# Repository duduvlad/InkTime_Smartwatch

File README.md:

# InkTime Smartwatch

Un smartwatch open-source cu ecran E-Paper, construit în jurul SoC-ului Nordic nRF52840. Proiectul acoperă etapa de Engineering Validation (EVT): design-ul hardware complet (schematic + PCB), fișierele de fabricație și modelul 3D al ansamblului.

## Cuprins

- [Diagrama Bloc](#diagrama-bloc)
- [Descriere Hardware](#descriere-hardware)
- [Pinout nRF52840](#pinout-nrf52840)
- [Bill of Materials](#bill-of-materials)
- [Estimare Consum Energetic](#estimare-consum-energetic)
- [Decizii de Design și Constrângeri](#decizii-de-design-și-constrângeri)
- [Imagini](#imagini)
- [Structura Repository-ului](#structura-repository-ului)
- [Licență](#licență)

---

## Diagrama Bloc
 
```
                          ┌─────────────────────────────────┐
                          │         nRF52840 (U1)           │
                          │       SoC + BLE Radio           │
                          │                                 │
          ┌───────────────┤ P0.06 (SDA)     P0.02 (SCK)    ├──── SPI ────┐
          │  I2C Bus      │ P0.07 (SCL)     P0.03 (MOSI)   │             │
          │               │                 P0.05 (CS)      │             │
          │               │                 P0.15 (DC)      │             │
          │               │                 P0.16 (RST)     │             │
          │               │                 P0.17 (BUSY)    │             │
          │               │                                 │             │
          │               │ P0.13 ──── SW_UP (buton)        │    ┌────────┴────────┐
          │               │ P0.14 ──── SW_ENTER (buton)     │    │  E-Paper 1.54"  │
          │               │ P1.02 ──── SW_DOWN (buton)      │    │  (via FPC J1)   │
          │               │                                 │    └─────────────────┘
          │               │ P0.12 ──── HAPTIC_EN (DRV2605)  │
          │               │ P0.08 ──── IMU_INT1             │
          │               │ P1.08 ──── IMU_INT2             │
          │               │ P0.10 ──── ALERT (fuel gauge)   │
          │               │ P0.11 ──── PMIC_INT (charger)   │
          │               │ P1.01 ──── EPD_PWR (MOSFET)     │
          │               │                                 │
          │               │ D+/D- ──── USB-C (J4)           │
          │               │ SWDIO/SWDCLK ── Debug (J2)      │
          │               │                                 │
          │               │ ANT (H23) ── Antenă 2.4GHz      │
          │               └─────────────────────────────────┘
          │
     ┌────┴─────────────────────────────────────────────────┐
     │                   Magistrala I2C                      │
     │   (SDA = P0.06, SCL = P0.07, pull-up 3.3kΩ)         │
     ├──────────────┬──────────────┬─────────────┬──────────┤
     │              │              │             │          │
┌────┴────┐  ┌─────┴─────┐  ┌────┴────┐  ┌────┴────┐     │
│ BMA423  │  │ DRV2605   │  │MAX17048 │  │BQ25180  │     │
│  (IC3)  │  │  (IC2)    │  │  (U3)   │  │ (IC1)   │     │
│  IMU    │  │ Haptic    │  │  Fuel   │  │ Charger │     │
│         │  │ Driver    │  │  Gauge  │  │         │     │
└─────────┘  └───────────┘  └────┬────┘  └────┬────┘     │
                                 │             │          │
                            ┌────┴─────────────┴────┐     │
                   ┌───────>│  Baterie LiPo 250mAh  │     │
                   │        │    AKYGA LP502030      │     │
                   │        └───────────┬────────────┘     │
                   │                    │ VREG (SYS)       │
              USB-C (J4)         ┌──────┴──────┐           │
              VBUS ─────────────>│  RT6160     │           │
                                 │  (IC9)      │           │
                                 │  Buck-Boost │           │
                                 └──────┬──────┘           │
                                        │                  │
                                    3.3V Rail ─────────────┘
```

---

## Descriere Hardware

Inima proiectului este **nRF52840** — un SoC cu procesor ARM Cortex-M4F la 64 MHz, 1 MB Flash și 256 KB RAM, plus radio BLE 5.0 integrat. Pe lângă logica principală, el controlează direct toate perifericele de pe placă.

**Managementul energiei** funcționează într-un lanț: USB-C → BQ25180 (charger LiPo) → baterie AKYGA LP502030 (250 mAh, 3.7V) → RT6160 (buck-boost) → 3.3V stabil pentru tot sistemul. Tensiunea bateriei este monitorizată de un fuel gauge MAX17048, care trimite alerte prin I2C și pin-ul ALERT când bateria scade sub praguri configurabile. Charger-ul BQ25180 comunică și el pe I2C, permițând configurarea curentului de încărcare, iar pin-ul !INT semnalează evenimente (încărcare completă, erori termice, etc.).

**Afișajul** este un ecran E-Paper de 1.54" conectat printr-un flex cable (FPC de 24 pini, conector Molex 503480-2400). E-Paper-ul consumă curent doar la refresh și își menține imaginea fără alimentare. Alimentarea display-ului este controlată separat prin P1.01, care comandă un MOSFET P-channel (DMG2305UX-7) — astfel display-ul poate fi oprit complet pentru a economisi energie. Comunicația cu display-ul se face pe SPI, cu pini adiționali de control (DC, RST, BUSY).

**Senzorul de mișcare** BMA421/BMA423 (accelerometru triaxial, 12 biți) este pe magistrala I2C și oferă două ieșiri de întrerupere (INT1 pe P0.08 și INT2 pe P1.08). Este folosit pentru numărarea pașilor, detecția gesturilor (raise-to-wake) și orientarea ecranului. Pin-ul SDO al senzorului este legat la GND prin R3, ceea ce setează adresa I2C la 0x18.

**Feedback haptic**: un motor de vibrații controlat de DRV2605 (driver dedicat cu bibliotecă internă de efecte). Driverul primește comenzi pe I2C și este activat/dezactivat de P0.12 (EN). Ieșirile OUT+ și OUT- merg la motorul haptic (shaker), cu test pad-uri pe placă pentru debugging.

**Butoanele**: trei butoane push (UP, ENTER, DOWN) cu rezistențe de pull-up de 10kΩ la 3.3V și condensatoare de debouncing de 1µF pe fiecare. Sunt active pe LOW — apăsarea trage pinul la GND.

**Conectivitate BLE**: antena ceramică Johanson 2450AT18B100E, conectată la pinul ANT al nRF52840 printr-o rețea de impedanță matching (L1 = 3.9nH, C3 = 1pF, C4 = 1pF). Zona de sub antenă este decupată din toate cele trei planuri de masă.

**Debug/Programare**: interfață SWD (SWDIO, SWDCLK) rutată la conectorul Tag-Connect TC2030-IDC (J2) și la test pad-uri. Pin-ul SWO (P1.00) este disponibil și el pe test pad pentru trace output.

---

## Pinout nRF52840

Tabelul de mai jos detaliază fiecare pin utilizat al microcontroller-ului, cu referința la ball-ul din pachetul aQFN (7x7 mm, 73 pini).

| Pin nRF52840 | Ball | Net / Semnal | Destinație | Notă |
|:---|:---|:---|:---|:---|
| P0.00/XL1 | D2 | P0.00/XL1 | Crystal 32.768 kHz (X2) | Low-frequency clock |
| P0.01/XL2 | F2 | P0.01/XL2 | Crystal 32.768 kHz (X2) | Low-frequency clock |
| P0.02/AIN0 | A12 | SCK | E-Paper SPI Clock | SPI master |
| P0.03/AIN1 | B13 | MOSI | E-Paper SPI Data | SPI master |
| P0.05/AIN3 | K2 | EPD_CS | E-Paper Chip Select | SPI CS, active LOW |
| P0.06 | L1 | SDA | Magistrala I2C - Data | BQ25180, BMA423, DRV2605, MAX17048 |
| P0.07 | M2 | SCL | Magistrala I2C - Clock | Pull-up 3.3kΩ la 3V3 |
| P0.08 | N1 | IMU_INT1 | BMA423 Interrupt 1 | Step counter, gesture detection |
| P0.10/NFC2 | J24 | ALERT | MAX17048 Battery Alert | Active LOW |
| P0.11 | T2 | PMIC_INT | BQ25180 !INT | Semnalizare stare încărcare |
| P0.12 | U1 | HAPTIC_EN | DRV2605 Enable | Activare driver haptic |
| P0.13 | AD8 | SW_UP | Buton UP | Pull-up 10kΩ (R5), debounce 1µF (C30) |
| P0.14 | AC9 | SW_ENTER | Buton ENTER | Pull-up 10kΩ (R8), debounce 1µF (C31) |
| P0.15 | AD10 | EPD_DC | E-Paper Data/Command | HIGH = date, LOW = comandă |
| P0.16 | AC11 | EPD_RST | E-Paper Reset | Active LOW |
| P0.17 | AD12 | EPD_BUSY | E-Paper Busy | HIGH = display ocupat |
| P0.18/RESET | AC13 | RESET | System Reset | Rutat la TP_RESET și J2 |
| P1.00 | AD22 | SWO | Serial Wire Output | Debug trace, rutat la TP_SWO |
| P1.01 | Y23 | EPD_PWR | MOSFET gate (DMG2305UX) | Controlează alimentarea display-ului |
| P1.02 | W24 | SW_DOWN | Buton DOWN | Pull-up 10kΩ (R7), debounce 1µF (C29) |
| P1.08 | P2 | IMU_INT2 | BMA423 Interrupt 2 | Al doilea canal de întrerupere |
| D+ | AD6 | D+ | USB-C Data+ | Prin ESD protection (USBLC6-2SC6Y) |
| D- | AD4 | D- | USB-C Data- | Prin ESD protection (USBLC6-2SC6Y) |
| VBUS | AD2 | VBUS | USB VBUS sense | Detectare conexiune USB |
| SWDIO | AC24 | SWDIO | SWD Debug Data | Rutat la J2 (TC2030) și TP |
| SWDCLK | AA24 | SWDCLK | SWD Debug Clock | Rutat la J2 (TC2030) și TP |
| XC1 | B24 | - | Crystal 32 MHz (X1) | High-frequency clock |
| XC2 | A23 | - | Crystal 32 MHz (X1) | High-frequency clock |
| ANT | H23 | ANT | Rețea matching + Antenă | 2.4 GHz BLE |
| VDDH | Y2 | 3V3 | Alimentare high voltage | 3.3V |
| VDD (multiple) | W1, AD14, B1, A22, AD23 | 3V3 | Alimentare digitală | Fiecare cu condensator de decuplare |
| DCC | B3 | - | DC/DC inductor intern | L2 (10µH) |
| DEC1-6 | diverse | - | Decoupling intern nRF | Condensatoare conform datasheet-ului |

**Pini liberi** (neconectați, disponibili pentru extensii viitoare): P0.04, P0.09, P0.19–P0.31, P1.03–P1.07, P1.09–P1.15.

---

## Bill of Materials

### Componente principale

| Componentă | MFR Part Number | Descriere | JLCPCB Part # | Datasheet |
|:---|:---|:---|:---|:---|
| nRF52840 (U1) | NRF52840-QFAA | SoC BLE 5.0, ARM Cortex-M4F, aQFN-73 | [C190794](https://jlcpcb.com/partdetail/NordicSemicon-NRF52840_QIAAR/C190794) | [Nordic](https://infocenter.nordicsemi.com/pdf/nRF52840_PS_v1.8.pdf) |
| BQ25180 (IC1) | BQ25180YBGR | Charger LiPo, I2C configurabil, BGA-8 | [C3682423](https://jlcpcb.com/partdetail/TexasInstruments-BQ25180YBGR/C3682423) | [TI](https://www.ti.com/lit/ds/symlink/bq25180.pdf) |
| DRV2605 (IC2) | DRV2605YZFR | Haptic driver ERM/LRA, I2C, BGA-9 | [C81079](https://jlcpcb.com/partdetail/TexasInstruments-DRV2605YZFR/C81079) | [TI](https://www.ti.com/lit/ds/symlink/drv2605.pdf) |
| BMA423 (IC3) | BMA423 | Accelerometru triaxial, 12-bit, I2C, LGA-12 | [C437656](https://jlcpcb.com/parts) | [Bosch](https://www.bosch-sensortec.com/media/boschsensortec/downloads/datasheets/bst-bma423-ds000.pdf) |
| RT6160 (IC9) | RT6160AWSC | Buck-Boost DC/DC, I2C, WL-CSP-15 | [C20621404](https://jlcpcb.com/parts) | [Richtek](https://www.richtek.com/assets/product_file/RT6160A/DS6160A-05.pdf) |
| MAX17048 (U3) | MAX17048G+T10 | Fuel gauge LiPo, I2C, TDFN-8 | [C2682616](https://jlcpcb.com/partdetail/MaximIntegrated-MAX17048GT10/C2682616) | [Analog Devices](https://datasheets.maximintegrated.com/en/ds/MAX17048-MAX17049.pdf) |
| Antenă BLE (ANT1) | 2450AT18B100E | Antenă ceramică 2.4 GHz, 1206 | - | [Johanson](https://www.johansontechnology.com/datasheets/2450AT18B100/2450AT18B100.pdf) |
| FPC Connector (J1) | 503480-2400 | Molex 24-pin FPC, 0.5mm pitch | - | [Molex](https://www.molex.com/en-us/products/part-detail/5034802400) |
| USB-C (J4) | KH-TYPE-C-16P | Connector USB-C 16 pini, Kinghelm | - | [Kinghelm](https://www.snapeda.com/parts/KH-TYPE-C-16P/Kinghelm/view-part/) |
| Tag-Connect (J2) | TC2030-IDC | Conector debug SWD, 6 pini | - | [Tag-Connect](https://www.tag-connect.com/product/tc2030-idc) |
| ESD Protection (D3) | USBLC6-2SC6Y | TVS diode array, USB ESD, SOT-23-6 | - | [ST](https://www.st.com/resource/en/datasheet/usblc6-2.pdf) |
| MOSFET P-ch | DMG2305UX-7 | P-MOSFET, 20V/4.2A, SOT-23 | - | [Diodes Inc.](https://www.diodes.com/assets/Datasheets/DMG2305UX.pdf) |
| MOSFET N-ch (Q3) | SI1308EDL-T1-GE3 | N-MOSFET, 30V/1.5A, SC-70 | - | [Vishay](https://www.vishay.com/docs/63399/si1308edl.pdf) |
| Schottky Diodes (D2,D4,D5) | MBR0530 | 30V/0.5A, SOD-123 | - | [ON Semi](https://www.onsemi.com/pdf/datasheet/mbr0520-d.pdf) |
| Butoane (x3) | EVP-AKE31A | Push button, Panasonic | - | [Panasonic](https://industrial.panasonic.com/cdbs/www-data/pdf/ATV0000/ATV0000CE3.pdf) |
| Crystal 32 MHz (X1) | - | XTAL 2016 package | - | - |
| Crystal 32.768 kHz (X2) | - | XTAL 3215 package | - | - |
| Inductor (L7) | FTC252012SR47MBCA | 0.47µH, 2520, TDK | [C5832368](https://jlcpcb.com/partdetail/6763488-FTC252012SR47MBCA/C5832368) | [TDK](https://product.tdk.com/en/search/inductor/inductor/smd/info?part_no=FTC252012SR47MBCA) |

### Pasive (sumarizat)

| Tip | Valori | Capsulă | Cantitate |
|:---|:---|:---|:---|
| Rezistențe 0201 | 0.47Ω, 2.2Ω, 3.3kΩ, 5.1kΩ, 7.68kΩ, 10kΩ | 0201 (0.6x0.3mm) | ~20 buc |
| Condensatoare ≤100nF | 1pF, 12pF, 47nF, 100pF, 100nF | 0201 | ~15 buc |
| Condensatoare >100nF | 1µF, 4.7µF, 10µF, 22µF | 0402 | ~25 buc |
| Inductori | 3.9nH, 10µH, 15µH, 68µH | 0402 | 4 buc |

Lista completă se regăsește în [`Manufacturing/BOM.csv`](Manufacturing/BOM.csv), iar coordonatele de asamblare în [`Manufacturing/PickAndPlace.csv`](Manufacturing/PickAndPlace.csv).

---

## Estimare Consum Energetic

Valorile sunt extrase din datasheet-urile componentelor, pentru modul activ și sleep.

| Componentă | Mod Activ | Mod Sleep / Idle | Notă |
|:---|:---|:---|:---|
| nRF52840 (CPU @ 64MHz) | ~5 mA | ~1.5 µA (System OFF) | CPU + Radio off în sleep |
| nRF52840 (BLE TX) | ~5–8 mA (0 dBm) | - | Transmisie BLE la 0 dBm |
| E-Paper 1.54" | ~15–25 mA (refresh) | ~0 µA | Consum doar la refresh, ~2-3s/refresh |
| BMA423 | ~150 µA | ~14 µA (low-power) | Accelerometru în modul low-power |
| MAX17048 | ~23 µA | ~3 µA (hibernate) | Fuel gauge, citiri periodice |
| BQ25180 | ~1 mA (charging) | ~1 µA (standby) | Consum propriu, fără curentul de încărcare |
| DRV2605 | ~10 mA (activ, cu motor) | ~650 µA (standby) | Standby cu EN LOW |
| RT6160 | ~30 µA (quiescent) | ~30 µA | Eficiența >90% la sarcini mici |

**Estimare viață baterie (250 mAh)**:
- *Standby pur* (ecran static, BLE off, CPU sleep): ~1.5µA + 14µA + 3µA + 1µA + 30µA ≈ **50 µA** → ~5000 ore (~208 zile)
- *Utilizare normală* (10 refresh-uri display/oră, BLE advertising, step counting): consum mediu estimat la **~0.3–0.5 mA** → ~500–830 ore (~21–35 zile)
- *Utilizare intensă* (BLE conectat, refresh-uri frecvente, haptic): consum mediu ~2–5 mA → ~2–5 zile

Aceste estimări sunt teoretice; consumul real va depinde de firmware și pattern-urile de utilizare.

---

## Decizii de Design și Constrângeri

### Reguli PCB respectate
- **Dimensiune PCB**: ~46 x 35 mm (forme octogonale cu decupaje pentru butoane), grosime 1 mm
- **Stackup 4 layere**:
  - **TOP**: componente + rutare + ground pour
  - **Inner 1**: rutare + ground pour
  - **Inner 2**: rutare + ground pour
  - **BOTTOM**: nefolosit (layer-ul a fost lăsat gol conform cerințelor)
- **Componente**: toate amplasate exclusiv pe TOP
- **Trasee de putere** (VBUS, VREG, 3V3, VBAT): width = 0.3 mm, subțiate doar sub BGA-uri unde spațiul impune
- **Trasee de date**: minimum 0.15 mm
- **Fără unghiuri de 90°** pe niciun traseu
- **Condensatoare de decuplare** (100nF): plasate imediat lângă pinii VDD ai fiecărui IC — în cazul nRF52840, câte un condensator per grup de pini VDD (C6, C7, C8, C12, C14 pe 3V3)
- **Via stitching** între cele trei planuri de masă (TOP, Inner 1, Inner 2), cu densitate crescută în zona circuitului radio pentru impedanță scăzută a căii de retur

### Antena
- Antena ceramică (ANT1) este plasată pe marginea de sus a PCB-ului (cea mai depărtată de corpul utilizatorului)
- **Decupaj complet** al cuprului sub antenă pe toate cele trei layere cu ground pour (TOP, Inner 1, Inner 2) — nicio rutare în acea zonă
- Rețea de matching: L1 (3.9nH), C3 (1pF), C4 (1pF) conform recomandărilor Nordic

### Alimentarea display-ului
- Display-ul E-Paper are nevoie de tensiuni de drive mari (±15V–20V) generate intern de circuitul display-ului
- Alimentarea display-ului este comutată printr-un MOSFET P-channel (DMG2305UX-7) controlat de P1.01 prin N-MOSFET Q3 (SI1308EDL)
- Circuitul include diode Schottky (MBR0530) pentru protecția tensiunilor inverse de la pompele de sarcină ale display-ului
- Inductorul L5 (68µH) și condensatoarele asociate filtrează alimentarea display-ului

### Bateria
- AKYGA LP502030: 250 mAh, 3.7V nominal, dimensiuni 32.5 × 21 × 5.5 mm
- Conectată direct la test pad-uri (TP_VBAT, TP_BAT_GND) prin lipire — nu se folosește conectorul JST pentru a economisi spațiu
- Modelul 3D al bateriei este inclus în ansamblul mecanic

### Test Pad-uri
Placa dispune de 14 test pad-uri marcate clar în silkscreen, permițând debugging fără nevoie de conectori:

| Test Pad | Semnal | Scop |
|:---|:---|:---|
| TP_3.3V / TP_3V3 | 3V3 | Verificare alimentare principală |
| TP_VREG | VREG/SYS | Ieșire charger → intrare DC/DC |
| TP_VBAT | VBAT | Tensiune baterie |
| TP_BAT_GND | GND | GND baterie (punct de lipire) |
| TP_GND | GND | Masă de referință |
| TP_SDA | SDA | I2C Data (debugging) |
| TP_SCL | SCL | I2C Clock (debugging) |
| TP_SWDIO | SWDIO | Debug SWD |
| TP_SWDCLK | SWDCLK | Debug SWD |
| TP_SWO | SWO | Serial Wire Output |
| TP_RESET | RESET | Reset manual |
| TP_OP | OUT+ | Ieșire haptic + |
| TP_ON | OUT- | Ieșire haptic - |

### DRC și ERC
- Design-ul trece verificarea DRC cu fișierul de reguli furnizat
- Erori acceptate și documentate:
  - **"Only INPUT pins on NET"** — eroare cosmetică, ignorată conform specificațiilor proiectului
  - **Overlap la test pad-uri** — TP-urile sunt dimensionate generos intenționat pentru ușurința accesului cu sonde
  - **Erori Dimension la butoane și USB-C** — cauzate de decupajele din conturul plăcii, neglijate conform cerințelor

### Silkscreen
- Layer-ul de silkscreen conține doar **designator-urile componentelor** (C1, R5, IC1 etc.), fără valori
- Test pad-urile sunt etichetate cu numele semnalelor pe care le poartă
- Orientarea textelor este uniformă pentru lizibilitate

---

## Imagini

### Schema electrică

**Pagina 1 — MCU, Power, IMU, SWD:**

**Pagina 2 — E-Paper, Haptic, Butoane, USB-C:**

### Layout PCB (TOP)

### PCB3D

### CARCASA

---

## Structura Repository-ului

```
InkTime_Smartwatch/
├── Hardware/
│   ├── Schematic.sch          # Schema electrică (Eagle/Fusion 360)
│   └── PCB.brd                # Layout-ul PCB (Eagle/Fusion 360)
├── Manufacturing/
│   ├── gerbers.zip            # Fișiere Gerber pentru fabricație PCB
│   ├── BOM.bom                # Bill of Materials complet
│   └── PickAndPlace.cpl       # Coordonate de asamblare SMT
├── Mechanical/
│   ├── WearAwareNewCase.step  # Model 3D complet (PCB + baterie + display + carcasă)
│   └── WearAwareNewCase.3mf   # Model 3D format 3MF
│   └── PCB.step                   # Model 3D al PCB-ului cu componente
├── Images/
│   ├── Schematic1.jpeg       # Schema electrică - MCU, Power, IMU, SWD
│   ├── Schematic2.jpeg # Schema electrică - E-Paper, Haptic, USB-C
│   └── Pcb.jpeg            # Layout PCB - vedere TOP
│   ├── PCB3D.jpeg                 # Randare 3D a PCB-ului
│   └── Carcasa.jpeg               # Randare carcasă
├── LICENSE                    # Apache License 2.0
└── README.md                  # Acest fișier
```

---

## Licență

Proiect open-source, licențiat sub [Apache License 2.0](LICENSE).

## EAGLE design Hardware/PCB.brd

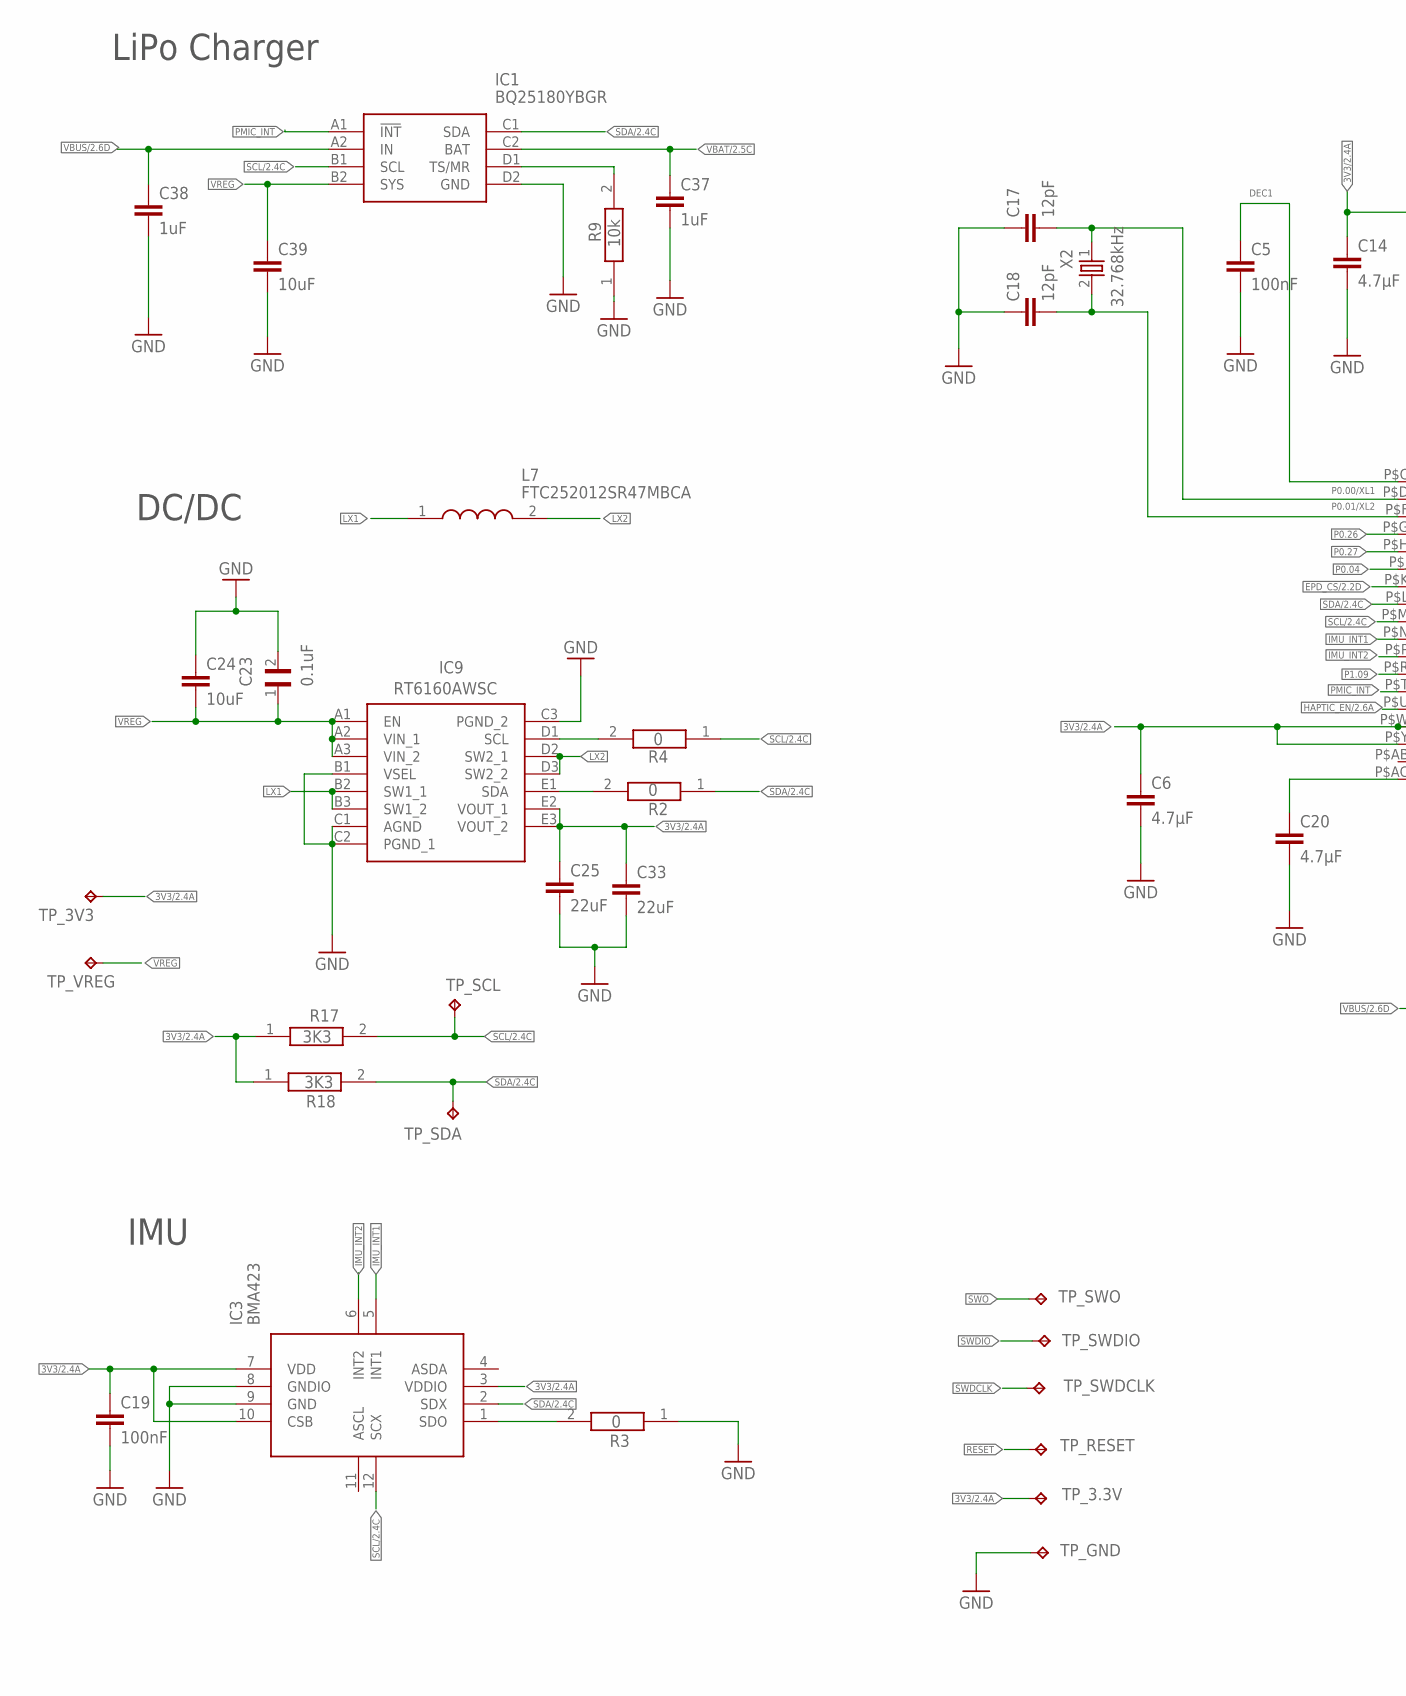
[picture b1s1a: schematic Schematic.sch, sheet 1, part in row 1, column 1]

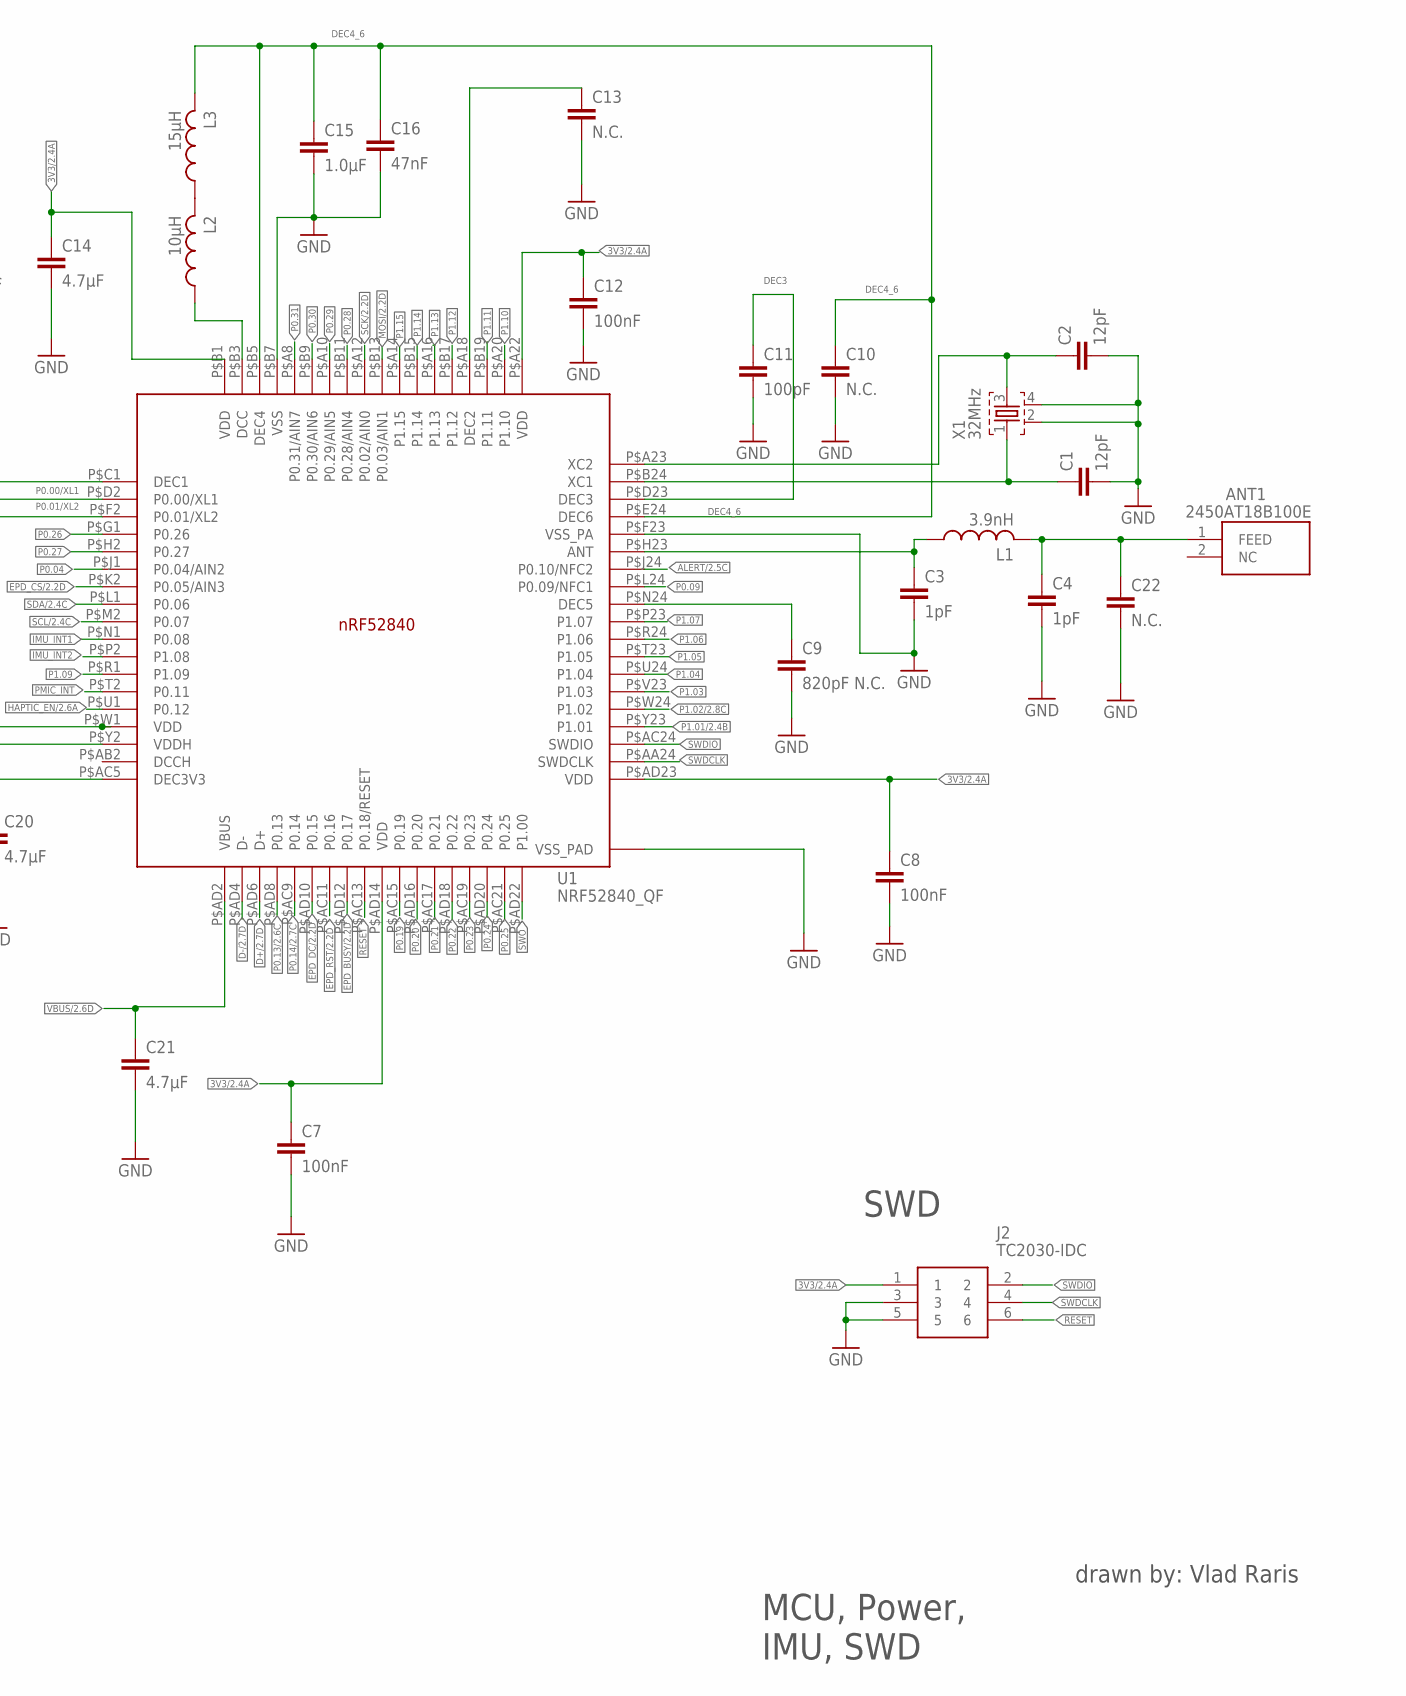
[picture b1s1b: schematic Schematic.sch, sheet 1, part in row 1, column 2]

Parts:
ANT1: 2450AT18B100E; 2450AT18B100E_ANTC3216X140N
C1, C2, C17, C18: 12pF; NORDIC_NRF_3_RESC0201_L
C3, C4: 1pF; NORDIC_NRF_3_RESC0201_L
C5, C7, C8, C12: 100nF; NORDIC_NRF_3_RESC0201_L
C6, C14, C20, C21: 4.7μF; PERFECT_0402_0402
C9: 820pF N.C.; NORDIC_NRF_3_RESC0201_L
C10, C13, C22: N.C.; NORDIC_NRF_3_RESC0201_L
C11: 100pF; NORDIC_NRF_3_RESC0201_L
C15: 1.0μF; PERFECT_0402_0402
C16: 47nF; NORDIC_NRF_3_RESC0201_L
C19: 100nF; PERFECT_0402_0402
C23: 0.1uF; GRM011R60J152KE01L_1_0201
C24, C39: 10uF; PERFECT_0402_0402
C25, C33: 22uF; PERFECT_0402_0402
C37, C38: 1uF; PERFECT_0402_0402
IC1: BQ25180YBGR; BQ25180YBGR_BGA8C40P2X4_100X155X50
IC3: BMA423; BMA423_BMA423
IC9: RT6160AWSC; RT6160AWSC_BGA15C40P3X5_140X230X60
J2: TC2030-IDC; TC2030-IDC_TC2030IDC
L1: 3.9nH; NORDIC_NRF_2_RESC0402_L
L2: 10μH; NORDIC_NRF_2_RESC0402_L
L3: 15μH; NORDIC_NRF_2_RESC0402_L
L7: FTC252012SR47MBCA; MLP2016SR47MT0S1_INDC2016X100N
R2, R3, R4: 0; CPF0201D7K68C1_0201
R9: 10k; CPF0201D7K68C1_0201
R17, R18: 3K3; CPF0201D7K68C1_0201
TP_3.3V, TP_3V3: HECTOR_WATCH_1_TPTP20R; HECTOR_WATCH_1_TP20R
TP_GND: HECTOR_WATCH_1_TPTP20R; HECTOR_WATCH_1_TP20R
TP_RESET: HECTOR_WATCH_1_TPTP20R; HECTOR_WATCH_1_TP20R
TP_SCL: HECTOR_WATCH_1_TPTP20R; HECTOR_WATCH_1_TP20R
TP_SDA: HECTOR_WATCH_1_TPTP20R; HECTOR_WATCH_1_TP20R
TP_SWDCLK: HECTOR_WATCH_1_TPTP20R; HECTOR_WATCH_1_TP20R
TP_SWDIO: HECTOR_WATCH_1_TPTP20R; HECTOR_WATCH_1_TP20R
TP_SWO: HECTOR_WATCH_1_TPTP20R; HECTOR_WATCH_1_TP20R
TP_VREG: HECTOR_WATCH_1_TPTP20R; HECTOR_WATCH_1_TP20R
U1: NRF52840_QF; NORDIC_NRF_4_AQFN50P700X700X85_HS-74N
X1: 32MHz; NORDIC_NRF_BT-XTAL_2016_N
X2: 32.768kHz; NORDIC_NRF_1_XTAL_3215_N

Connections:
3V3/2.4A: C6.1, C7.1, C8.1, C12.1, C14.1, C19.1, C25.1, C33.1, IC3.3 (VDDIO), IC3.7 (VDD), IC3.10 (CSB), IC9.E2 (VOUT_1), IC9.E3 (VOUT_2), J2.1, R17.1, R18.1, TP_3.3V.TP, TP_3V3.TP, U1.P$A22 (VDD), U1.P$AD14 (VDD), U1.P$AD23 (VDD), U1.P$B1 (VDD), U1.P$W1 (VDD), U1.P$Y2 (VDDH)
ALERT/2.5C: U1.P$J24 (P0.10/NFC2)
D+/2.7D: U1.P$AD6 (D+)
D-/2.7D: U1.P$AD4 (D-)
DEC1: C5.1, U1.P$C1 (DEC1)
DEC3: C11.1, U1.P$D23 (DEC3)
DEC4_6: C10.1, C15.1, C16.1, L3.2, U1.P$B5 (DEC4), U1.P$E24 (DEC6)
EPD_BUSY/2.2D: U1.P$AD12 (P0.17)
EPD_CS/2.2D: U1.P$K2 (P0.05/AIN3)
EPD_DC/2.2D: U1.P$AD10 (P0.15)
EPD_RST/2.2D: U1.P$AC11 (P0.16)
GND: C1.2, C2.2, C3.2, C4.2, C5.2, C6.2, C7.2, C8.2, C9.2, C10.2, C11.2, C12.2, C13.2, C14.2, C15.2, C16.2, C17.1, C18.1, C19.2, C20.2, C21.2, C22.2, C23.2, C24.1, C25.2, C33.2, C37.2, C38.2, C39.2, IC1.D2 (GND), IC3.8 (GNDIO), IC3.9 (GND), IC9.B1 (VSEL), IC9.C1 (AGND), IC9.C2 (PGND_1), IC9.C3 (PGND_2), J2.3, J2.5, R3.1, R9.1, TP_GND.TP, U1.P$74 (VSS_PAD), U1.P$75 (VSS_PAD), U1.P$76 (VSS_PAD), U1.P$77 (VSS_PAD), U1.P$78 (VSS_PAD), U1.P$79 (VSS_PAD), U1.P$80 (VSS_PAD), U1.P$81 (VSS_PAD), U1.P$82 (VSS_PAD), U1.P$83 (VSS_PAD), U1.P$84 (VSS_PAD), U1.P$85 (VSS_PAD), U1.P$86 (VSS_PAD), U1.P$87 (VSS_PAD), U1.P$88 (VSS_PAD), U1.P$89 (VSS_PAD), U1.P$90 (VSS_PAD), U1.P$B7 (VSS), U1.P$F23 (VSS_PA), X1.2, X1.4; also elsewhere on the board
HAPTIC_EN/2.6A: U1.P$U1 (P0.12)
IMU_INT1: IC3.5 (INT1), U1.P$N1 (P0.08)
IMU_INT2: IC3.6 (INT2), U1.P$P2 (P1.08)
LX1: IC9.B2 (SW1_1), IC9.B3 (SW1_2), L7.1
LX2: IC9.D2 (SW2_1), IC9.D3 (SW2_2), L7.2
MOSI/2.2D: U1.P$B13 (P0.03/AIN1)
unnamed: IC1.D1 (TS/MR), R9.2
unnamed: IC9.D1 (SCL), R4.2
unnamed: IC9.E1 (SDA), R2.2
unnamed: C20.1, U1.P$AC5 (DEC3V3)
unnamed: C9.1, U1.P$N24 (DEC5)
unnamed: C3.1, L1.1, U1.P$H23 (ANT)
unnamed: IC3.1 (SDO), R3.2
unnamed: C1.1, U1.P$B24 (XC1), X1.1
unnamed: C13.1, U1.P$A18 (DEC2)
unnamed: ANT1.1 (FEED), C4.1, C22.1, L1.2
unnamed: C2.1, U1.P$A23 (XC2), X1.3
unnamed: L2.2, L3.1
unnamed: L2.1, U1.P$B3 (DCC)
P0.00/XL1: C17.2, U1.P$D2 (P0.00/XL1), X2.1
P0.01/XL2: C18.2, U1.P$F2 (P0.01/XL2), X2.2
P0.04: U1.P$J1 (P0.04/AIN2)
P0.09: U1.P$L24 (P0.09/NFC1)
P0.13/2.6C: U1.P$AD8 (P0.13)
P0.14/2.7C: U1.P$AC9 (P0.14)
P0.19: U1.P$AC15 (P0.19)
P0.20: U1.P$AD16 (P0.20)
P0.21: U1.P$AC17 (P0.21)
P0.22: U1.P$AD18 (P0.22)
P0.23: U1.P$AC19 (P0.23)
P0.24: U1.P$AD20 (P0.24)
P0.25: U1.P$AC21 (P0.25)
P0.26: U1.P$G1 (P0.26)
P0.27: U1.P$H2 (P0.27)
P0.28: U1.P$B11 (P0.28/AIN4)
P0.29: U1.P$A10 (P0.29/AIN5)
P0.30: U1.P$B9 (P0.30/AIN6)
P0.31: U1.P$A8 (P0.31/AIN7)
P1.01/2.4B: U1.P$Y23 (P1.01)
P1.02/2.8C: U1.P$W24 (P1.02)
P1.03: U1.P$V23 (P1.03)
P1.04: U1.P$U24 (P1.04)
P1.05: U1.P$T23 (P1.05)
P1.06: U1.P$R24 (P1.06)
P1.07: U1.P$P23 (P1.07)
P1.09: U1.P$R1 (P1.09)
P1.10: U1.P$A20 (P1.10)
P1.11: U1.P$B19 (P1.11)
P1.12: U1.P$B17 (P1.12)
P1.13: U1.P$A16 (P1.13)
P1.14: U1.P$B15 (P1.14)
P1.15: U1.P$A14 (P1.15)
PMIC_INT: IC1.A1 (!INT), U1.P$T2 (P0.11)
RESET: J2.6, TP_RESET.TP, U1.P$AC13 (P0.18/RESET)
SCK/2.2D: U1.P$A12 (P0.02/AIN0)
SCL/2.4C: IC1.B1 (SCL), IC3.12 (SCX), R4.1, R17.2, TP_SCL.TP, U1.P$M2 (P0.07)
SDA/2.4C: IC1.C1 (SDA), IC3.2 (SDX), R2.1, R18.2, TP_SDA.TP, U1.P$L1 (P0.06)
SWDCLK: J2.4, TP_SWDCLK.TP, U1.P$AA24 (SWDCLK)
SWDIO: J2.2, TP_SWDIO.TP, U1.P$AC24 (SWDIO)
SWO: TP_SWO.TP, U1.P$AD22 (P1.00)
VBAT/2.5C: C37.1, IC1.C2 (BAT)
VBUS/2.6D: C21.1, C38.1, IC1.A2 (IN), U1.P$AD2 (VBUS)
VREG: C23.1, C24.2, C39.1, IC1.B2 (SYS), IC9.A1 (EN), IC9.A2 (VIN_1), IC9.A3 (VIN_2), TP_VREG.TP

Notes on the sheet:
LiPo Charger
DC/DC
SWD
IMU
drawn by: Vlad Raris
MCU, Power, IMU, SWD

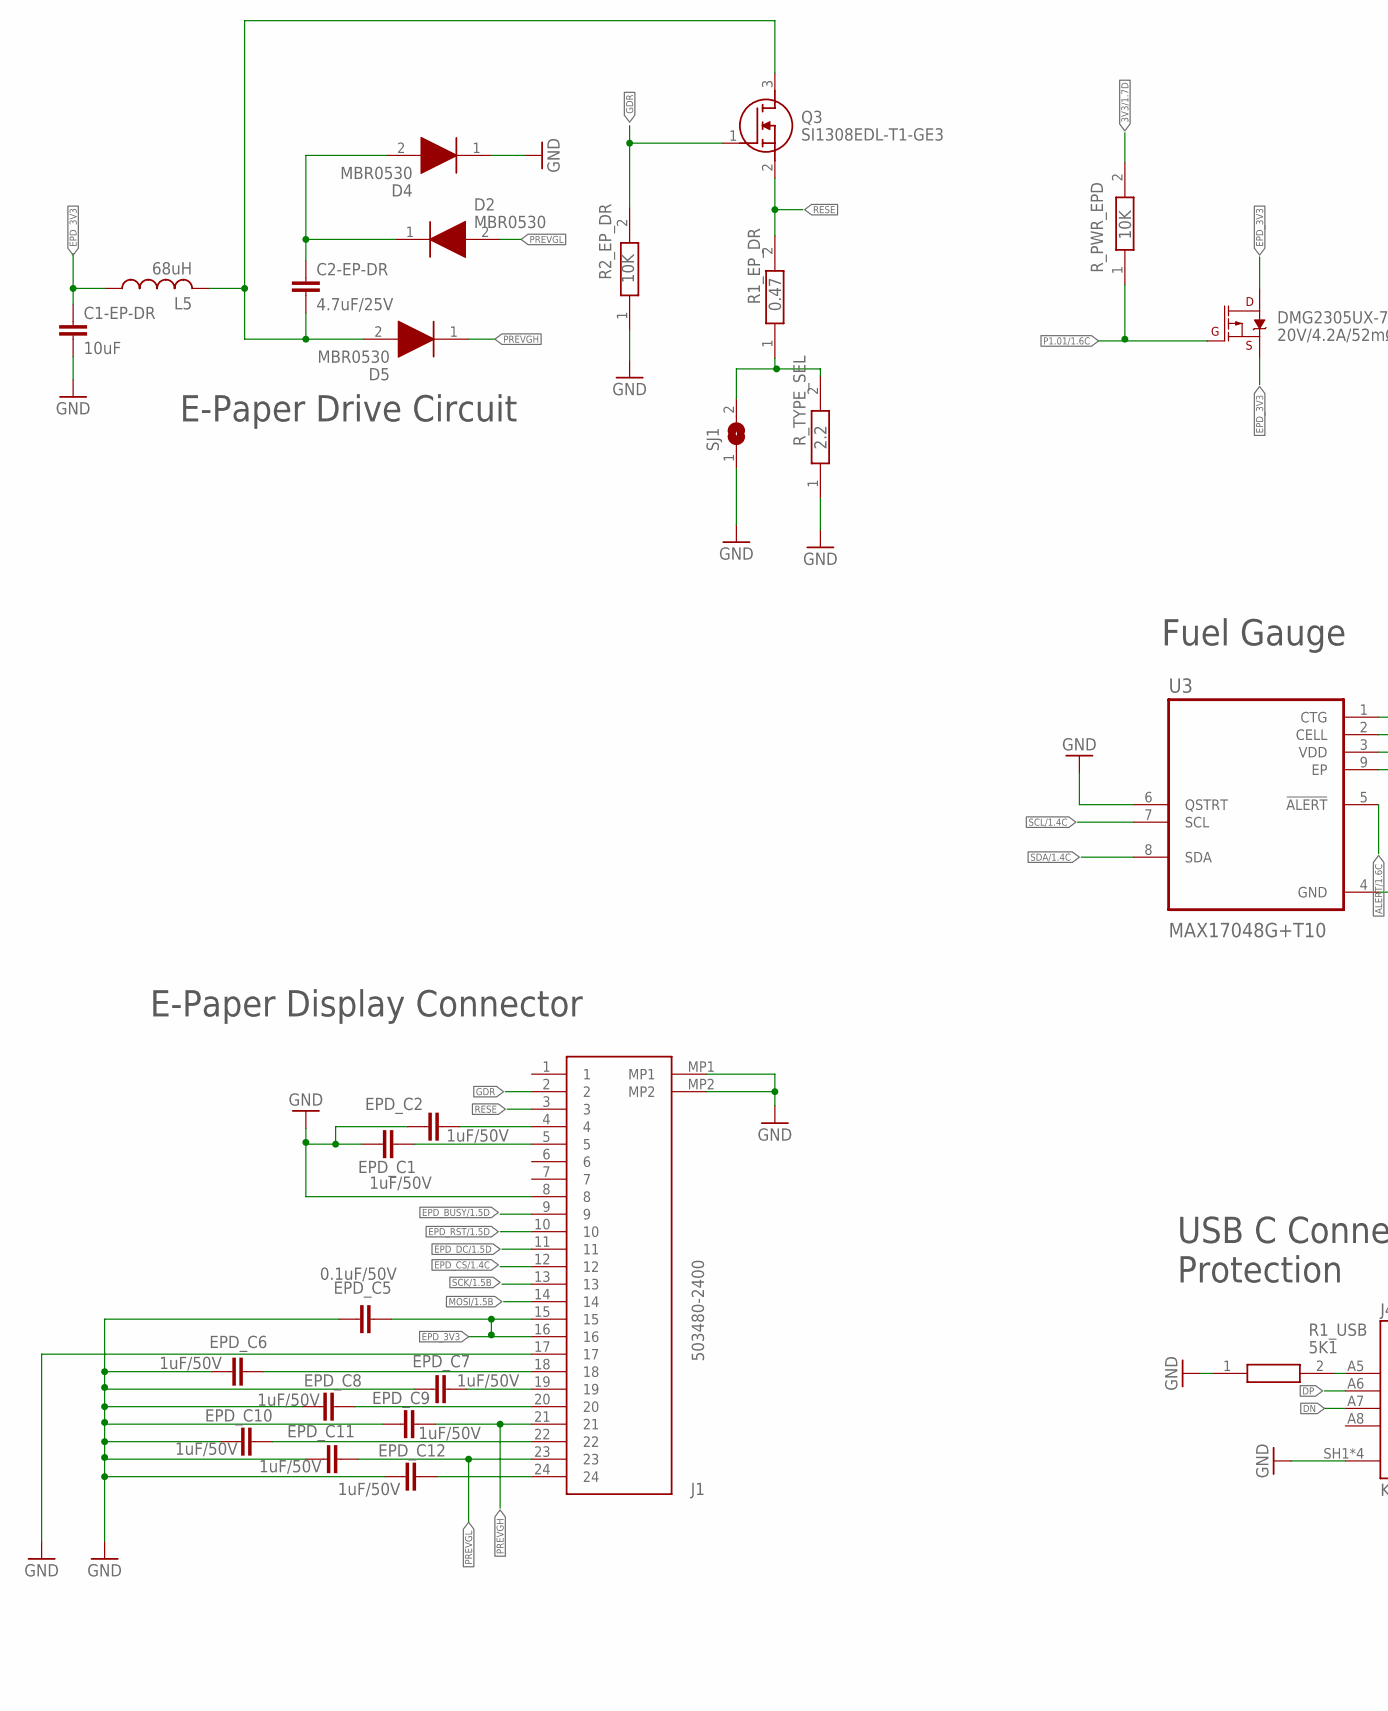
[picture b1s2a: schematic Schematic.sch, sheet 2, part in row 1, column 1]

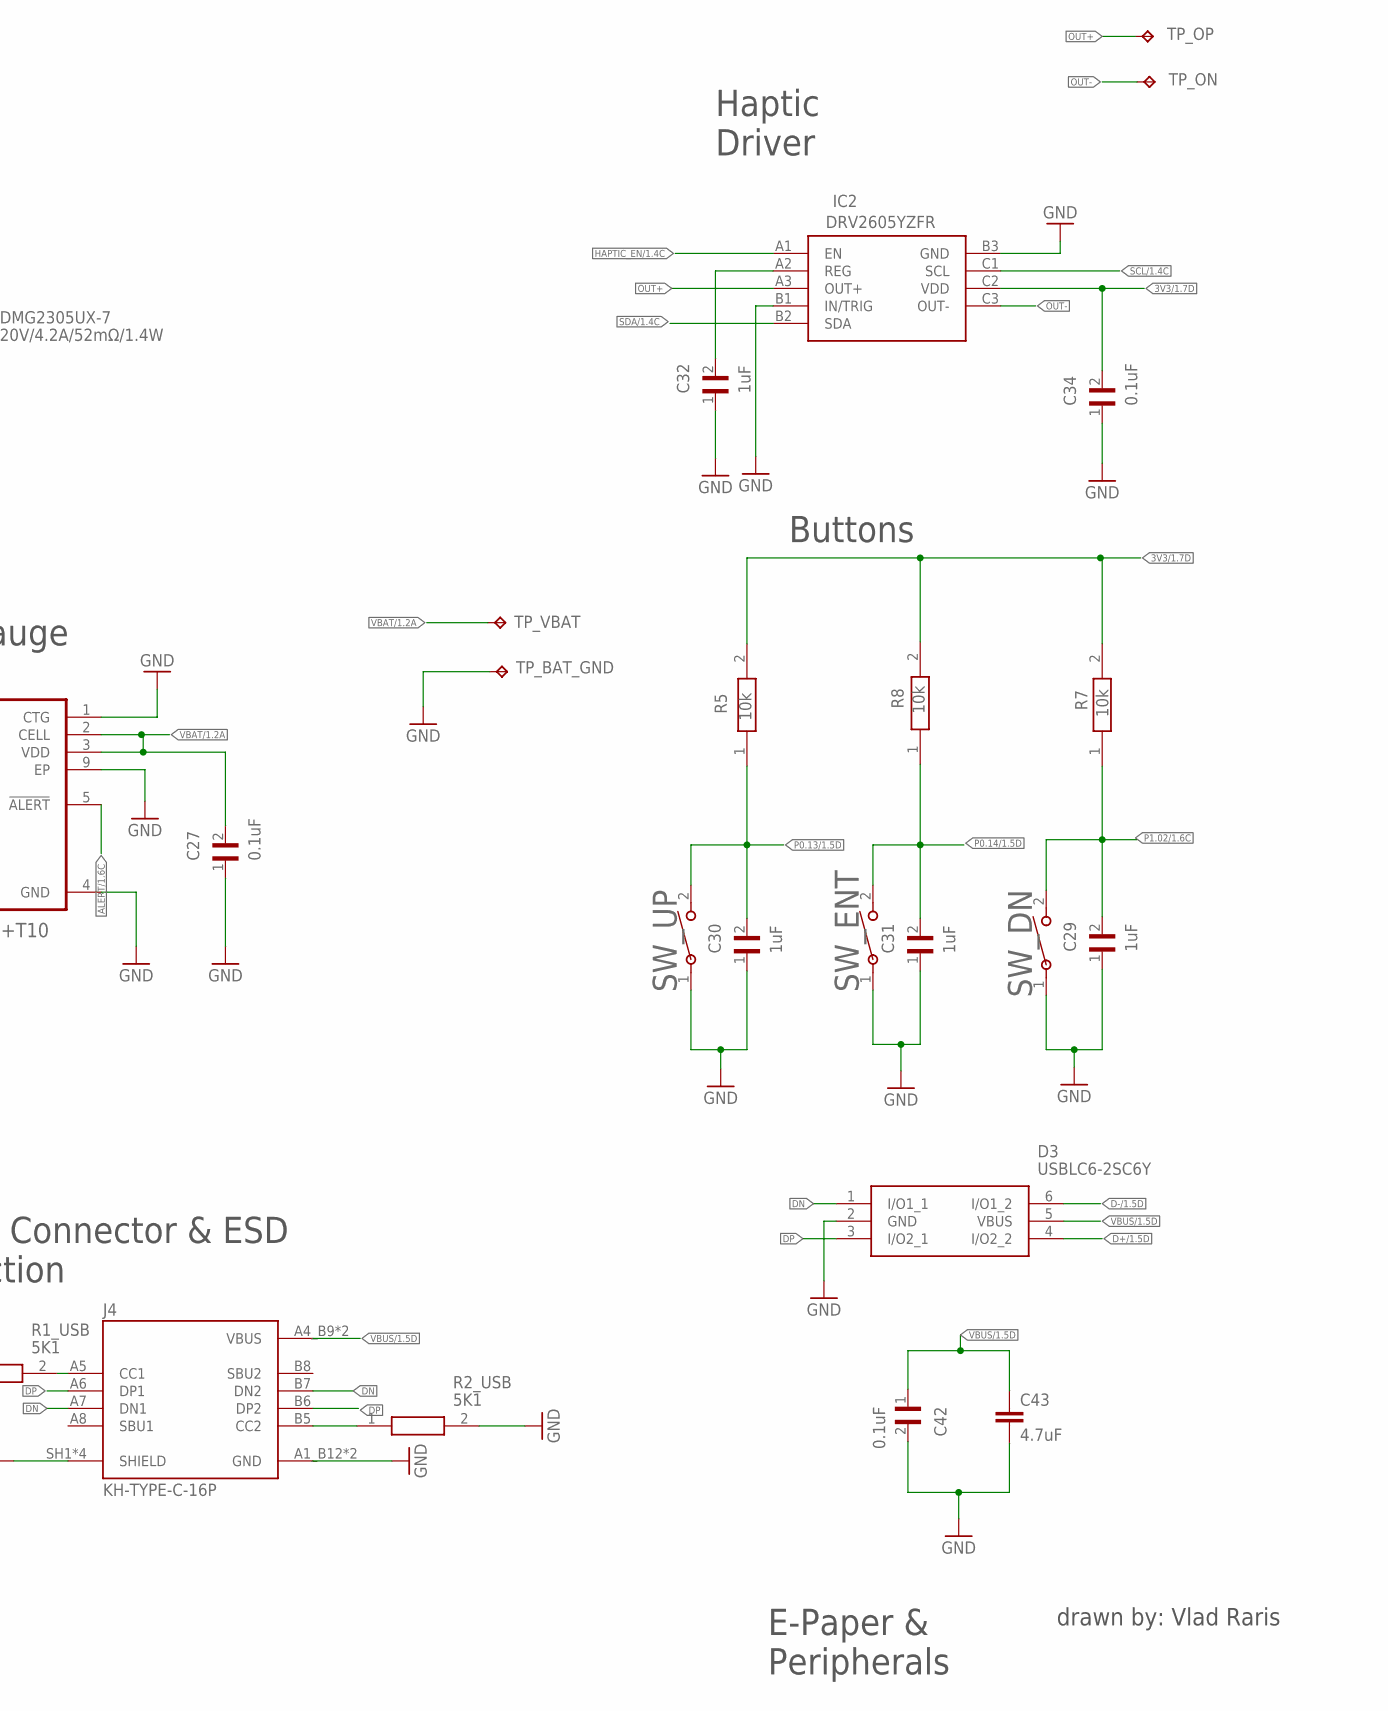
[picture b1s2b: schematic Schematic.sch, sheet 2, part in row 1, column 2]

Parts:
C1-EP-DR: 10uF; NORDIC_NRF_3_RESC0201_L
C2-EP-DR: 4.7uF/25V; PERFECT_0402_0402
C27, C34, C42: 0.1uF; GRM011R60J152KE01L_2_CAPC0201X13N
C29, C30, C31, C32: 1uF; GRM011R60J152KE01L_2_CAPC0201X13N
C43: 4.7uF; PERFECT_0402_0402
D2, D4, D5: MBR0530; ESP32_C6_LIBRARY_5_SOD3716X135N
D3: USBLC6-2SC6Y; ESP32_C6_LIBRARY_3_SOT95P280X145-6N
DMG2305UX-7: 20V/4.2A/52mΩ/1.4W; ESP32_C6_LIBRARY_4_ESP32_C6_LIBRARY_4_ESP32_C6_LIBRARY_4_ES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
EPD_C1, EPD_C2, EPD_C6, EPD_C7, EPD_C8, EPD_C9, EPD_C10, EPD_C11, EPD_C12: 1uF/50V; PERFECT_0402_0402
EPD_C5: 0.1uF/50V; PERFECT_0402_0402
IC2: DRV2605YZFR; DRV2605YZFR_BGA9C50P3X3_144X144X62
J1: 503480-2400; 503480-2400_5034802400
J4: KH-TYPE-C-16P; KH-TYPE-C-16P_KINGHELM_KH-TYPE-C-16P
L5: 68uH; NORDIC_NRF_2_RESC0402_L
Q3: SI1308EDL-T1-GE3; ESP32_C6_LIBRARY_6_SOT65P210X110-3N
R1_EP_DR: 0.47; CPF0201D7K68C1_0201
R1_USB, R2_USB: 5K1; CPF0201D7K68C1_0201
R2_EP_DR: 10K; CPF0201D7K68C1_0201
R5, R7, R8: 10k; CPF0201D7K68C1_0201
R_PWR_EPD: 10K; CPF0201D7K68C1_0201
R_TYPE_SEL: 2.2; CPF0201D7K68C1_0201
SJ1: ESP32_C6_LIBRARY_7_JUMPER_SJ
SW_DN: 2025-10-22_07-23-44_LIBRARY_EVP-AKE31ASW_EVP-AKE3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; 2025-10-22_07-23-44_LIBRARY_SW_EVP-AKE31A_PAN
SW_ENT: 2025-10-22_07-23-44_LIBRARY_EVP-AKE31ASW_EVP-AKE3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; 2025-10-22_07-23-44_LIBRARY_SW_EVP-AKE31A_PAN
SW_UP: 2025-10-22_07-23-44_LIBRARY_EVP-AKE31ASW_EVP-AKE3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; 2025-10-22_07-23-44_LIBRARY_SW_EVP-AKE31A_PAN
TP_BAT_GND: HECTOR_WATCH_1_TPTP20R; HECTOR_WATCH_1_TP20R
TP_ON: HECTOR_WATCH_1_TPTP20R; HECTOR_WATCH_1_TP20R
TP_OP: HECTOR_WATCH_1_TPTP20R; HECTOR_WATCH_1_TP20R
TP_VBAT: HECTOR_WATCH_1_TPTP20R; HECTOR_WATCH_1_TP20R
U3: MAX17048G+T10; ESP32_C6_LIBRARY_SON50P200X200X80-9N

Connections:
3V3/1.7D: C34.2, IC2.C2 (VDD), R5.2, R7.2, R8.2, R_PWR_EPD.2
ALERT/1.6C: U3.5 (!ALERT)
D+/1.5D: D3.4 (I/O2_2)
D-/1.5D: D3.6 (I/O1_2)
DN: D3.1 (I/O1_1), J4.A7 (DN1), J4.B7 (DN2)
DP: D3.3 (I/O2_1), J4.A6 (DP1), J4.B6 (DP2)
EPD_3V3: C1-EP-DR.1, DMG2305UX-7.2 (S), DMG2305UX-7.3 (D), EPD_C5.2, J1.15, J1.16, L5.1
EPD_BUSY/1.5D: J1.9
EPD_CS/1.4C: J1.12
EPD_DC/1.5D: J1.11
EPD_RST/1.5D: J1.10
GDR: J1.2, Q3.1 (G), R2_EP_DR.2
GND: C1-EP-DR.2, C27.1, C29.1, C30.1, C31.1, C32.1, C34.1, C42.2, C43.2, D3.2 (GND), D4.1 (K), EPD_C1.1, EPD_C2.1, EPD_C5.1, EPD_C6.1, EPD_C7.1, EPD_C8.1, EPD_C9.1, EPD_C10.1, EPD_C11.1, EPD_C12.1, IC2.B1 (IN/TRIG), IC2.B3 (GND), J1.8, J1.17, J1.MP1, J1.MP2, J4.A1_B12 (GND), J4.A12_B1 (GND), J4.SH1 (SHIELD), J4.SH2 (SHIELD), J4.SH3 (SHIELD), J4.SH4 (SHIELD), R1_USB.1, R2_EP_DR.1, R2_USB.2, R_TYPE_SEL.1, SJ1.1, SW_DN.1, SW_ENT.1, SW_UP.1, TP_BAT_GND.TP, U3.1 (CTG), U3.4 (GND), U3.6 (QSTRT), U3.9 (EP); also elsewhere on the board
HAPTIC_EN/1.4C: IC2.A1 (EN)
MOSI/1.5B: J1.14
unnamed: C2-EP-DR.1, D2.1 (K), D4.2 (A)
unnamed: C2-EP-DR.2, D5.2 (A), L5.2, Q3.3 (D)
unnamed: J4.B5 (CC2), R2_USB.1
unnamed: R1_EP_DR.1, R_TYPE_SEL.2, SJ1.2
unnamed: C32.2, IC2.A2 (REG)
unnamed: J4.A5 (CC1), R1_USB.2
unnamed: EPD_C6.2, J1.18
unnamed: EPD_C7.2, J1.19
unnamed: EPD_C8.2, J1.20
unnamed: EPD_C10.2, J1.22
unnamed: EPD_C12.2, J1.24
unnamed: EPD_C2.2, J1.4
unnamed: EPD_C1.2, J1.5
OUT+: IC2.A3 (OUT+), TP_OP.TP
OUT-: IC2.C3 (OUT-), TP_ON.TP
P0.13/1.5D: C30.2, R5.1, SW_UP.2
P0.14/1.5D: C31.2, R8.1, SW_ENT.2
P1.01/1.6C: DMG2305UX-7.1 (G), R_PWR_EPD.1
P1.02/1.6C: C29.2, R7.1, SW_DN.2
PREVGH: D5.1 (K), EPD_C9.2, J1.21
PREVGL: D2.2 (A), EPD_C11.2, J1.23
RESE: J1.3, Q3.2 (S), R1_EP_DR.2
SCK/1.5B: J1.13
SCL/1.4C: IC2.C1 (SCL), U3.7 (SCL)
SDA/1.4C: IC2.B2 (SDA), U3.8 (SDA)
VBAT/1.2A: C27.2, TP_VBAT.TP, U3.2 (CELL), U3.3 (VDD)
VBUS/1.5D: C42.1, C43.1, D3.5 (VBUS), J4.A4_B9 (VBUS), J4.A9_B4 (VBUS)

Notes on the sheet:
E-Paper Drive Circuit
E-Paper & Peripherals
drawn by: Vlad Raris
E-Paper Display Connector
Fuel Gauge
Buttons
USB C Connector & ESD Protection
Haptic Driver

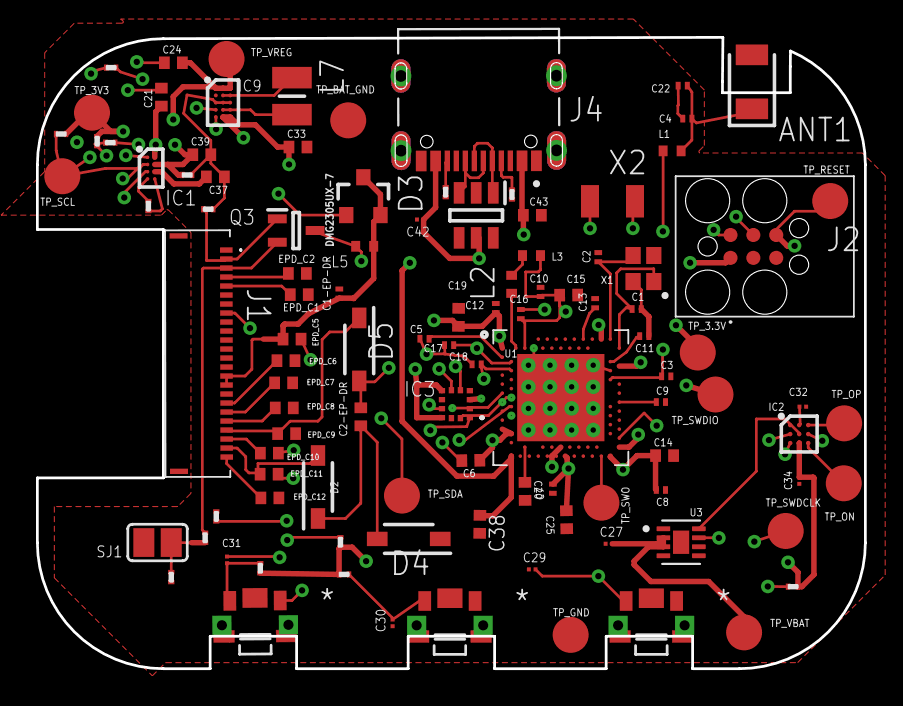
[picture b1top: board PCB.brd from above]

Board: 4 copper layers, 46.0 x 35.1 mm, 105 parts (0 on the bottom side), 65 nets.

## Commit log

2026-04-10 Enhance README with images and PCB layout info
    Added images and updated PCB layout details in README.
2026-04-10 Rename Schematic2.jpeg to Schematic.jpeg
2026-04-10 Rename Schematic1.jpeg to Schematic2.jpeg
2026-04-10 Rename Schematic.jpeg to Schematic1.jpeg
2026-04-10 Rename Schematic1.jpeg to Schematic.jpeg
2026-04-10 Rename Schematic2.jpeg to Schematic1.jpeg
2026-04-17 Rename BOM.csv to BOM.bom
2026-04-17 Rename PickAndPlace.csv to PickAndPlace.cpl
2026-04-21 Add BOM.bom file to Manufacturing directory
2026-04-21 Rename WhatsApp Image 2026-04-21 at 09.37.19.jpeg to Carcasa
2026-04-21 Rename WhatsApp Image 2026-04-21 at 11.17.51.jpeg to PCB3D
2026-04-21 Rename Carcasa to Carcasa.jpeg
2026-04-21 Rename PCB3D to PCB3D.jpeg
2026-04-21 Add diagram for nRF52840 in README

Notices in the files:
parts and their libraries:
COPYRIGHT: Copyright (C) 2025 Ultra Librarian. All rights reserved.
